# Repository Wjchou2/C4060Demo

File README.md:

# C4060Demo
Using the <a href="https://www.st.com/resource/en/datasheet/m74hc4060.pdf">C4060 IC</a> to time different LED blinks
<br>
The C4060Demo is a board that allows you to test the speeds that the C4060 IC generates, by using LED indicators. I made this project for Resolution Hardware Week 3, to practice reading datasheets and using ICs, and how to turn these into a real PCB board in KiCad. The power is supplied by an external battery that you can connect easily via the labled power pins on the left side of the board. To use, insert an LED into a 2 pin header on the right, each set of VCC and GND pins should have a longer and longer blink delay as you go down.
<h1>Schematic</h1>
View the live KiCanvas PCB link
<a href="https://kicanvas.org/?repo=https%3A%2F%2Fgithub.com%2FWjchou2%2FC4060Demo%2Ftree%2Fmain%2Fkicad">here</a>
<br>

<h1>PCB and 3D Render</h1>

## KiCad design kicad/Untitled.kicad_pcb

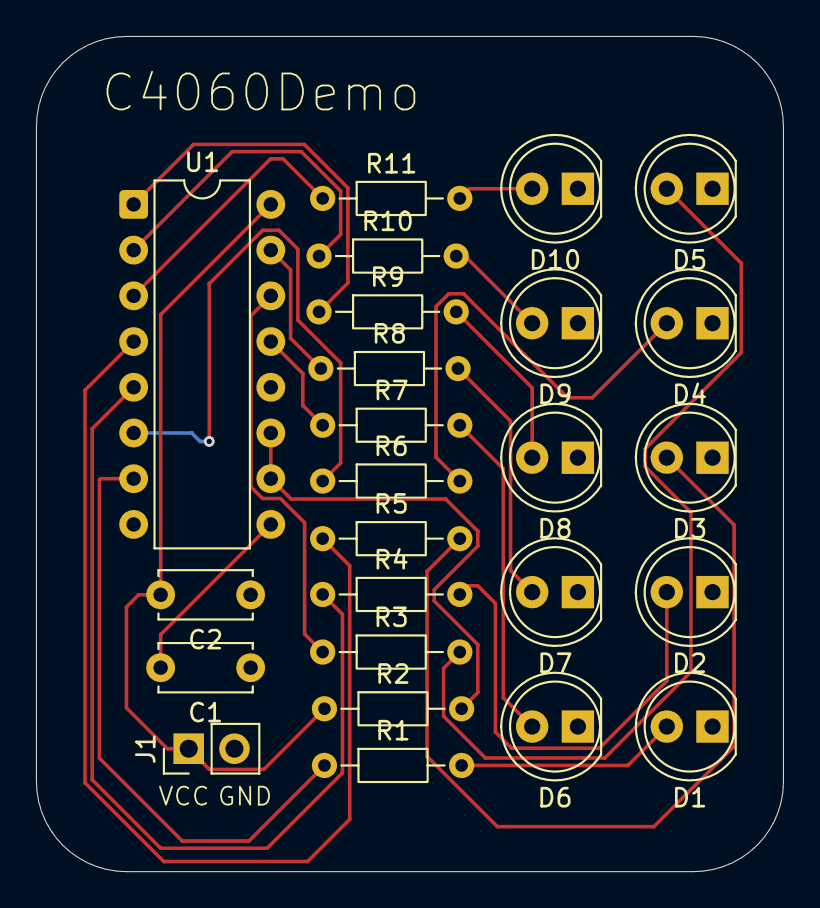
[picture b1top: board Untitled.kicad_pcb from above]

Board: 2 copper layers, 41.5 x 46.4 mm, 25 parts (0 on the bottom side), 24 nets.

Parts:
C1: 1µF; C_Disc_D5.0mm_W2.5mm_P5.00mm
C2: 0.1; C_Disc_D5.0mm_W2.5mm_P5.00mm
D1, D2, D3, D4, D5, D6, D7, D8, D9, D10: LED; LED_D5.0mm
J1: Conn_01x02; PinHeader_1x02_P2.54mm_Vertical
R1, R3, R4, R5, R6, R7, R8, R9, R10, R11: 300; R_Axial_DIN0204_L3.6mm_D1.6mm_P7.62mm_Horizontal
R2: 100kΩ; R_Axial_DIN0204_L3.6mm_D1.6mm_P7.62mm_Horizontal
U1: 4060; DIP-16_W7.62mm

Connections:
GND: C1.1, C2.1, D1.1 (K), D2.1 (K), D3.1 (K), D4.1 (K), D5.1 (K), D6.1 (K), D7.1 (K), D8.1 (K), D9.1 (K), D10.1 (K), J1.2, U1.8 (VSS), U1.12 (CLR)
unnamed: D1.2 (A), R1.2
unnamed: D2.2 (A), R4.2
unnamed: D3.2 (A), R5.2
unnamed: D4.2 (A), R6.2
unnamed: D5.2 (A), R3.2
unnamed: D6.2 (A), R7.2
unnamed: D7.2 (A), R8.2
unnamed: D8.2 (A), R9.2
unnamed: D9.2 (A), R10.2
unnamed: D10.2 (A), R11.2
unnamed: R1.1, U1.7 (Q4)
unnamed: R4.1, U1.5 (Q5)
unnamed: R5.1, U1.4 (Q6)
unnamed: R6.1, U1.6 (Q7)
unnamed: R3.1, U1.14 (Q8)
unnamed: R7.1, U1.13 (Q9)
unnamed: R8.1, U1.15 (Q10)
unnamed: R9.1, U1.1 (Q12)
unnamed: R10.1, U1.2 (Q13)
unnamed: R11.1, U1.3 (Q14)
unnamed: C1.2, U1.9 (~Φ0)
unnamed: R2.2, U1.10 (Φ0), U1.11 (~Φ1)
VCC: C2.2, J1.1, R2.1, U1.16 (VDD)

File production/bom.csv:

Designator,Footprint,Quantity,Value,LCSC Part #
C1,C_Disc_D5.0mm_W2.5mm_P5.00mm,1,1µF,
C2,C_Disc_D5.0mm_W2.5mm_P5.00mm,1,0.1,
"D1, D10, D2, D3, D4, D5, D6, D7, D8, D9",LED_D5.0mm,10,LED,
J1,PinHeader_1x02_P2.54mm_Vertical,1,Conn_01x02,
"R1, R10, R11, R3, R4, R5, R6, R7, R8, R9",R_Axial_DIN0204_L3.6mm_D1.6mm_P7.62mm_Horizontal,10,300,
R2,R_Axial_DIN0204_L3.6mm_D1.6mm_P7.62mm_Horizontal,1,100kΩ,
U1,DIP-16_W7.62mm,1,4060,
